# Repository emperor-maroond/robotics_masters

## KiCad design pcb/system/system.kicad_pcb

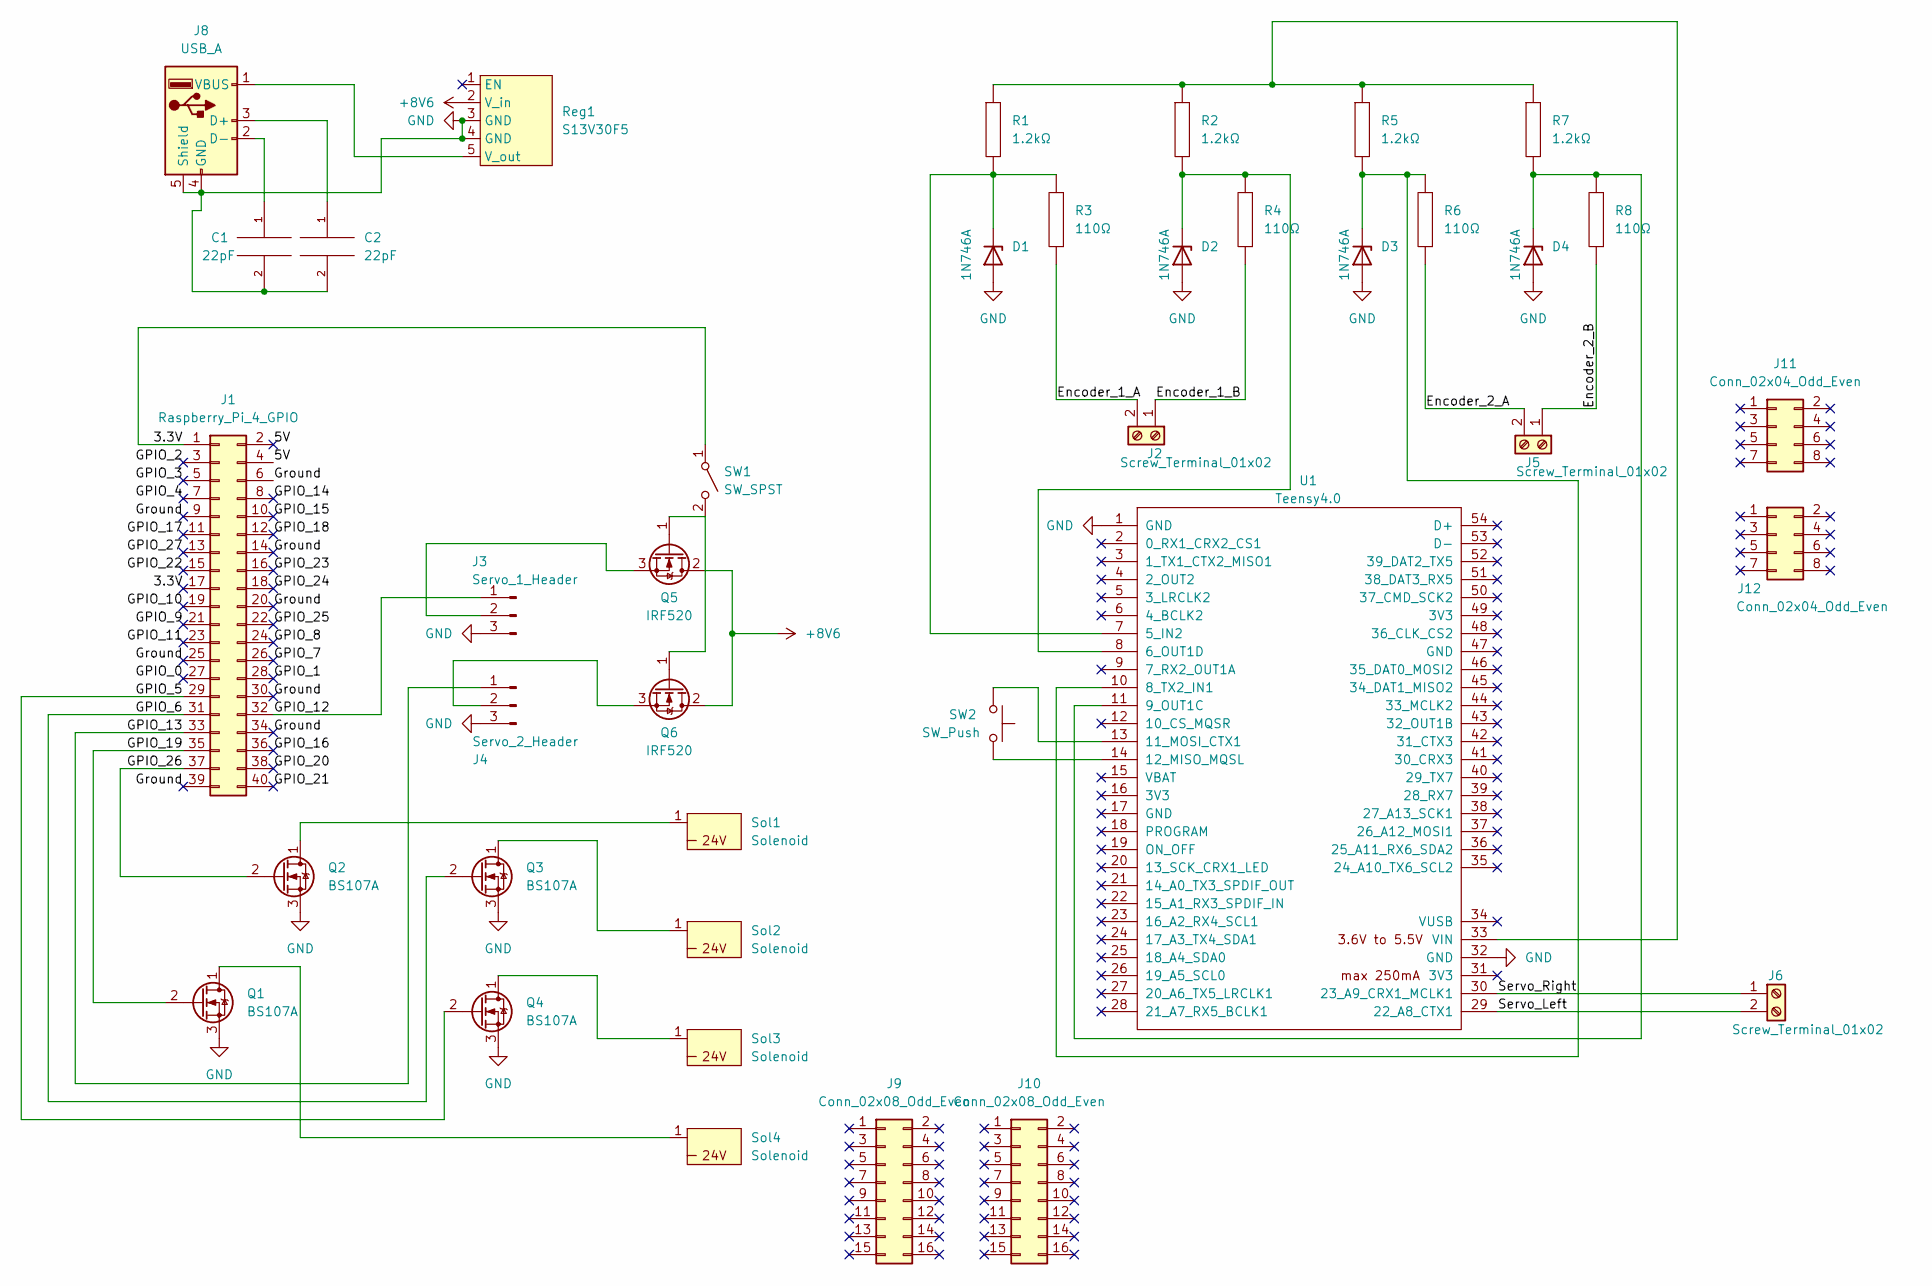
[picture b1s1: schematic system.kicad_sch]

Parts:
C1, C2: 22pF; CP_Radial_Tantal_D4.5mm_P2.50mm
D1, D2, D3, D4: 1N746A; D_DO-35_SOD27_P7.62mm_Horizontal
J1: Raspberry_Pi_4_GPIO; PinHeader_2x20_P2.54mm_Vertical
J2, J5, J6: Screw_Terminal_01x02; TerminalBlock_4Ucon_1x02_P3.50mm_Vertical
J3: Servo_1_Header; PinHeader_1x03_P2.54mm_Vertical
J4: Servo_2_Header; PinHeader_1x03_P2.54mm_Vertical
J8: USB_A; USB_A_Molex_105057_Vertical
J9, J10: Conn_02x08_Odd_Even; PinHeader_2x08_P2.54mm_Vertical
J11, J12: Conn_02x04_Odd_Even; PinHeader_2x04_P2.54mm_Vertical
Q1, Q2, Q3, Q4: BS107A; TO-92L_HandSolder
Q5, Q6: IRF520; TO-92_HandSolder
R1, R2, R5, R7: 1.2kΩ; R_Axial_DIN0204_L3.6mm_D1.6mm_P5.08mm_Horizontal
R3, R4, R6, R8: 110Ω; R_Axial_DIN0204_L3.6mm_D1.6mm_P5.08mm_Horizontal
Reg1: S13V30F5; PinSocket_1x05_P2.54mm_Vertical
SW1: SW_SPST; SW_CuK_JS202011CQN_DPDT_Straight
SW2: SW_Push; SW_PUSH_6mm_H4.3mm
Sol1, Sol2, Sol3, Sol4: Solenoid; PinSocket_1x01_P2.54mm_Vertical
U1: Teensy4.0; Teensy40

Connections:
+8V: Q5.2 (D), Q6.2 (D), Reg1.2 (V_in)
/3.3V: J1.1, J1.17, SW1.1 (A)
/5V: J1.2, J1.4
/Encoder_1_A: J2.2, R3.1
/Encoder_1_B: J2.1, R4.1
/Encoder_2_A: J5.2, R6.1
/Encoder_2_B: J5.1, R8.1
/GPIO_0: J1.27
/GPIO_1: J1.28
/GPIO_2: J1.3
/GPIO_3: J1.5
/GPIO_4: J1.7
/GPIO_5: J1.29, Q4.2 (G)
/GPIO_6: J1.31, Q3.2 (G)
/GPIO_7: J1.26
/GPIO_8: J1.24
/GPIO_9: J1.21
/GPIO_10: J1.19
/GPIO_11: J1.23
/GPIO_12: J1.32, J3.1
/GPIO_13: J1.33, J4.1
/GPIO_14: J1.8
/GPIO_15: J1.10
/GPIO_16: J1.36
/GPIO_17: J1.11
/GPIO_18: J1.12
/GPIO_19: J1.35, Q1.2 (G)
/GPIO_20: J1.38
/GPIO_21: J1.40
/GPIO_22: J1.15
/GPIO_23: J1.16
/GPIO_24: J1.18
/GPIO_25: J1.22
/GPIO_26: J1.37, Q2.2 (G)
/GPIO_27: J1.13
/Ground: J1.6, J1.9, J1.14, J1.20, J1.25, J1.30, J1.34, J1.39
/Servo_Left: J6.2, U1.29 (22_A8_CTX1)
/Servo_Right: J6.1, U1.30 (23_A9_CRX1_MCLK1)
GND: C1.2, C2.2, D1.2 (A), D2.2 (A), D3.2 (A), D4.2 (A), J3.3, J4.3, J8.4 (GND), J8.5 (Shield), Q1.3 (S), Q2.3 (S), Q3.3 (S), Q4.3 (S), Reg1.3 (GND), Reg1.4 (GND), U1.1 (GND), U1.32 (GND)
unnamed: C1.1, J8.2 (D-)
unnamed: C2.1, J8.3 (D+)
unnamed: D1.1 (K), R1.2, R3.2, U1.7 (5_IN2)
unnamed: D2.1 (K), R2.2, R4.2, U1.8 (6_OUT1D)
unnamed: D3.1 (K), R5.2, R6.2, U1.10 (8_TX2_IN1)
unnamed: D4.1 (K), R7.2, R8.2, U1.11 (9_OUT1C)
unnamed: J3.2, Q5.3 (S)
unnamed: J4.2, Q6.3 (S)
unnamed: J8.1 (VBUS), Reg1.5 (V_out)
unnamed: Q1.1 (D), Sol4.1
unnamed: Q2.1 (D), Sol1.1
unnamed: Q3.1 (D), Sol2.1
unnamed: Q4.1 (D), Sol3.1
unnamed: Q5.1 (G), Q6.1 (G), SW1.2 (B)
unnamed: R1.1, R2.1, R5.1, R7.1, U1.33 (VIN)
unnamed: SW2.1, U1.13 (11_MOSI_CTX1)
unnamed: SW2.2, U1.14 (12_MISO_MQSL)

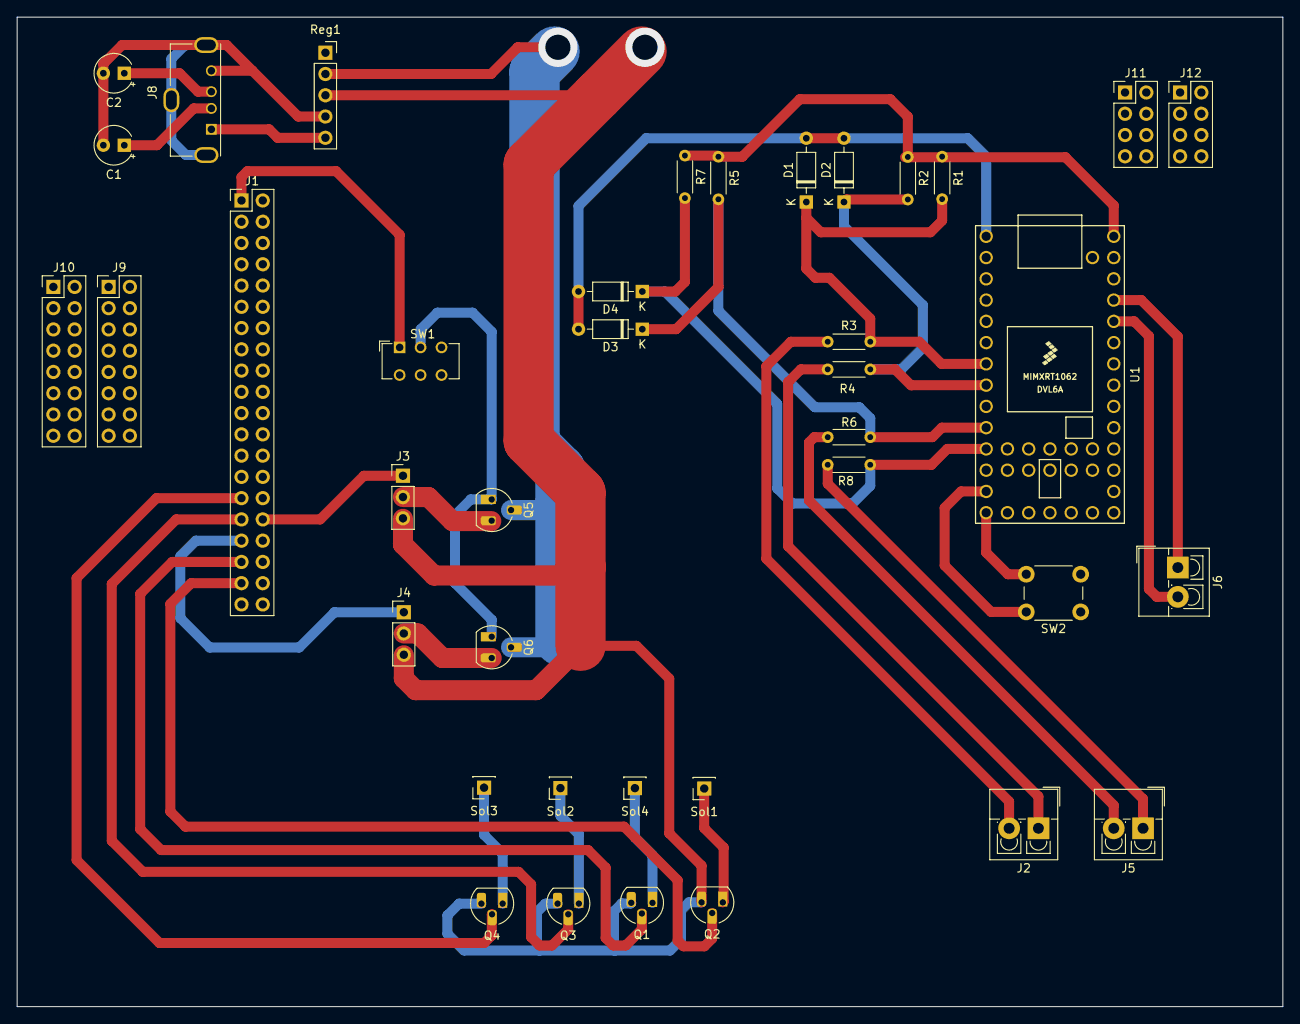
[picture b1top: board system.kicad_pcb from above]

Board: 2 copper layers, 151.2 x 118.2 mm, 39 parts (0 on the bottom side), 34 nets.

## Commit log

2021-03-15 Updated my code
2021-03-15 asdsad
2021-03-16 jaaa
2021-03-17 still not working
2021-03-18 NOOO
2021-03-23 mkII
2021-03-23 it's ALIVE!!!
2021-03-24 some updates
2021-03-25 Nee dit is nie
2021-03-25 Push test
2021-03-25 Removed test file
2021-03-29 Tried to implement piston
2021-03-30 here we go again
2021-03-30 30 Mar: Its something
2021-03-31 reeee
2021-04-05 5 Apr
2021-04-05 yoyo
2021-04-06 bang bang seems to be fine now
2021-04-08 jou ma se P
2021-04-11 added hard stops, I think
2021-04-11 some changes
2021-04-11 removed some files and added backup folder
2021-04-12 tried hardstops... again
2021-04-13 fixed some bang-bang stuff
2021-04-13 i need a hero
2021-04-14 added empty monoped. going to see if I can make that work
2021-04-14 updated the monoped wih bang-bang
2021-04-15 got the monoped working and no trying to do the same to the biped
2021-04-19 finally got the biped hopping
2021-04-20 saved data to array
2021-04-20 looking at steady state step
2021-04-21 added constant vel
2021-04-24 added video folder
2021-04-26 26 Apr 10h
2021-04-26 added ros package
2021-04-26 started inserting contact orders
2021-04-28 tried adding contact order
2021-04-29 it works!
2021-04-30 I think is correct
2021-05-07 just a backup
2021-05-10 accel + decel
2021-05-11 pickled the steady-state data
2021-05-11 accel not working yet but getting there
2021-05-11 accel seems to be correct
2021-05-12 going to stitch movement
2021-05-12 stitched everything
2021-05-13 tried to force the model to be planar with prismatic joints. We'll see if it works
2021-05-17 busy with gazebo
2021-05-18 gazebo is a pain
2021-05-19 got Gazebo sorted
2021-05-19 added bin files
2021-06-22 swaped filed to a different folder
2021-06-22 updated model
2021-06-23 updated model as well as made some changes to the code to adjust for refrence points
2021-06-24 just backuped some code
2021-06-24 updated optimasation code
2021-07-02 ran optimisation so smaller epsilon and ran gazebo with it
2021-07-11 some init msg
2021-07-13 got everything working again
2021-07-14 writing ros code
2021-07-15 51 Jul
2021-07-16 new trajectories
2021-07-19 more trajectories
2021-07-20 updated ros code
2021-07-20 created my own message fil
2021-07-21 added message package
2021-07-21 can now send data
2021-07-22 new paths
2021-07-22 new trajec
2021-07-26 tried interpolation
2021-07-26 much better looking
2021-07-28 yes queen
2021-08-03 now interpolating data before publishing it
2021-08-03 removed useless files
2021-08-09 new stuff
2021-08-10 removed old files
2021-08-12 just making sure everything is up to date
2021-08-19 asss
2021-08-19 removed redundant folders
2021-08-30 new traject
2021-09-01 yeet rp
2021-09-01 can now recieve serial data
2021-09-05 added py file and removed useles folder
2021-09-05 added end condition to the data being send to the Pi
2021-09-06 improved my amazing code
2021-09-06 added lines to dump sensor data to a txt file on close
2021-09-09 short traject generated
2021-09-14 short trajec added
2021-10-07 updated trajec
2021-10-08 new traj
2021-10-11 can now recieve data and store it
2021-10-22 ass \
2021-10-26 I think I know what i got to do with my code
2021-10-27 code updated
2021-11-01 update the code to break the bot
2021-11-03 just readded some stuff
2021-11-11 added Gazebo hopping code
2021-11-11 updated gazebo code
2021-11-17 got the state maschine working
2021-11-18 update gazebo_ctrl code a little
2021-11-18 played around with some ros code
2021-11-22 made it so ctrl code takes avg
2021-11-24 code for ctrl should work
2021-11-24 correcterd subscriber
2021-11-30 code working, look at dumping to txt
2021-12-09 just made sure the avg is correct
2022-01-03 added ofset angel awa hop code
2022-01-12 removed the avg
2022-01-19 bug fixes
2022-01-25 updated freebody
2022-01-26 update optimisation and ros code
2022-01-26 ros code not wokring properly
2022-01-27 updated hop code\
2022-02-10 updated code
2022-02-14 14Feb
2022-02-16 did some stuff
2022-02-17 busy with free body stuff
2022-02-21 still need decel
2022-02-22 added more feasible stuff
2022-02-24 good soup
2022-02-24 pcb files
2022-02-25 pcb updated
2022-02-26 updated pcb
2022-03-01 copium
2022-03-02 still need to future proof pcb
2022-03-02 i think the pcb is done
2022-03-04 thicker pcb traces
2022-03-10 just making sure everything is pushed
2022-03-10 reduced torque and increased damping
2022-03-15 updated traj
2022-03-16 update opt code
2022-03-17 yeet
2022-03-17 updated open loop ctrl
2022-03-21 slower trajects
2022-03-25 NANIwget -N -t 5 -T 10 https://github.com/UbuntuForums/wireless-info/raw/master/wireless-info && chmod +x wireless-info && ./wireless-info
2022-03-28 updated damp_x2
2022-03-28 updated ctrl_ii
2022-03-29 updated ctrl
2022-04-01 data files
2022-04-06 main part of fix body
2022-04-06 data
2022-04-06 trying to remember filters
2022-04-07 maybe the filtering works
2022-04-13 updated some old traject and start with free bod
2022-04-28 updates to freebody stuff
2022-04-28 another
2022-04-29 designed untested freebody code
2022-05-03 rename cntrl code because of bracet
2022-05-17 added new freebody control stuff
2022-05-18 updated freebody conrtol code to take smaller steps
2022-05-19 more controller updates
2022-05-23 i am losing my mind
2022-06-06 update saved trajec for better data
2022-06-14 got something going. Add more steps
2022-07-14 added extra hop to controller
2022-07-20 freebody provided okayish traject
2022-07-21 new freebody data
2022-07-26 new freebod data that moves futher
2022-07-26 nice graphs for callen
2022-07-27 1 more freebod data
2022-07-28 updated limit cycle code
2022-08-01 updated fixed body data
2022-08-01 graphs
2022-08-02 free bod rough data
2022-08-08 two trajec with diff vel
2022-08-10 new data that is not good enough
2022-08-16 new free rough data
2022-08-18 one nice trajec
2022-08-19 trajec
2022-09-02 busy updaring gaze ctrl
2022-09-06 data from simu
2022-09-06 update to gazebo model and control
2022-09-12 added file with ugly name
2022-09-12 rename
2022-09-12 updates to graph code
2022-09-14 update to graphing
2022-09-16 nice looking traj
2022-09-27 update trajec
2022-10-07 update to graphs
2022-10-10 neutral point calc
2022-10-11 calculate neutral point
2022-10-11 scaled graphs
2022-10-12 I think i got all the graphs
2022-10-13 values should be done now
2022-10-18 graphssss
2022-10-18 magic
2022-11-14 updated graphing to split traj
2022-11-16 so many graphs
